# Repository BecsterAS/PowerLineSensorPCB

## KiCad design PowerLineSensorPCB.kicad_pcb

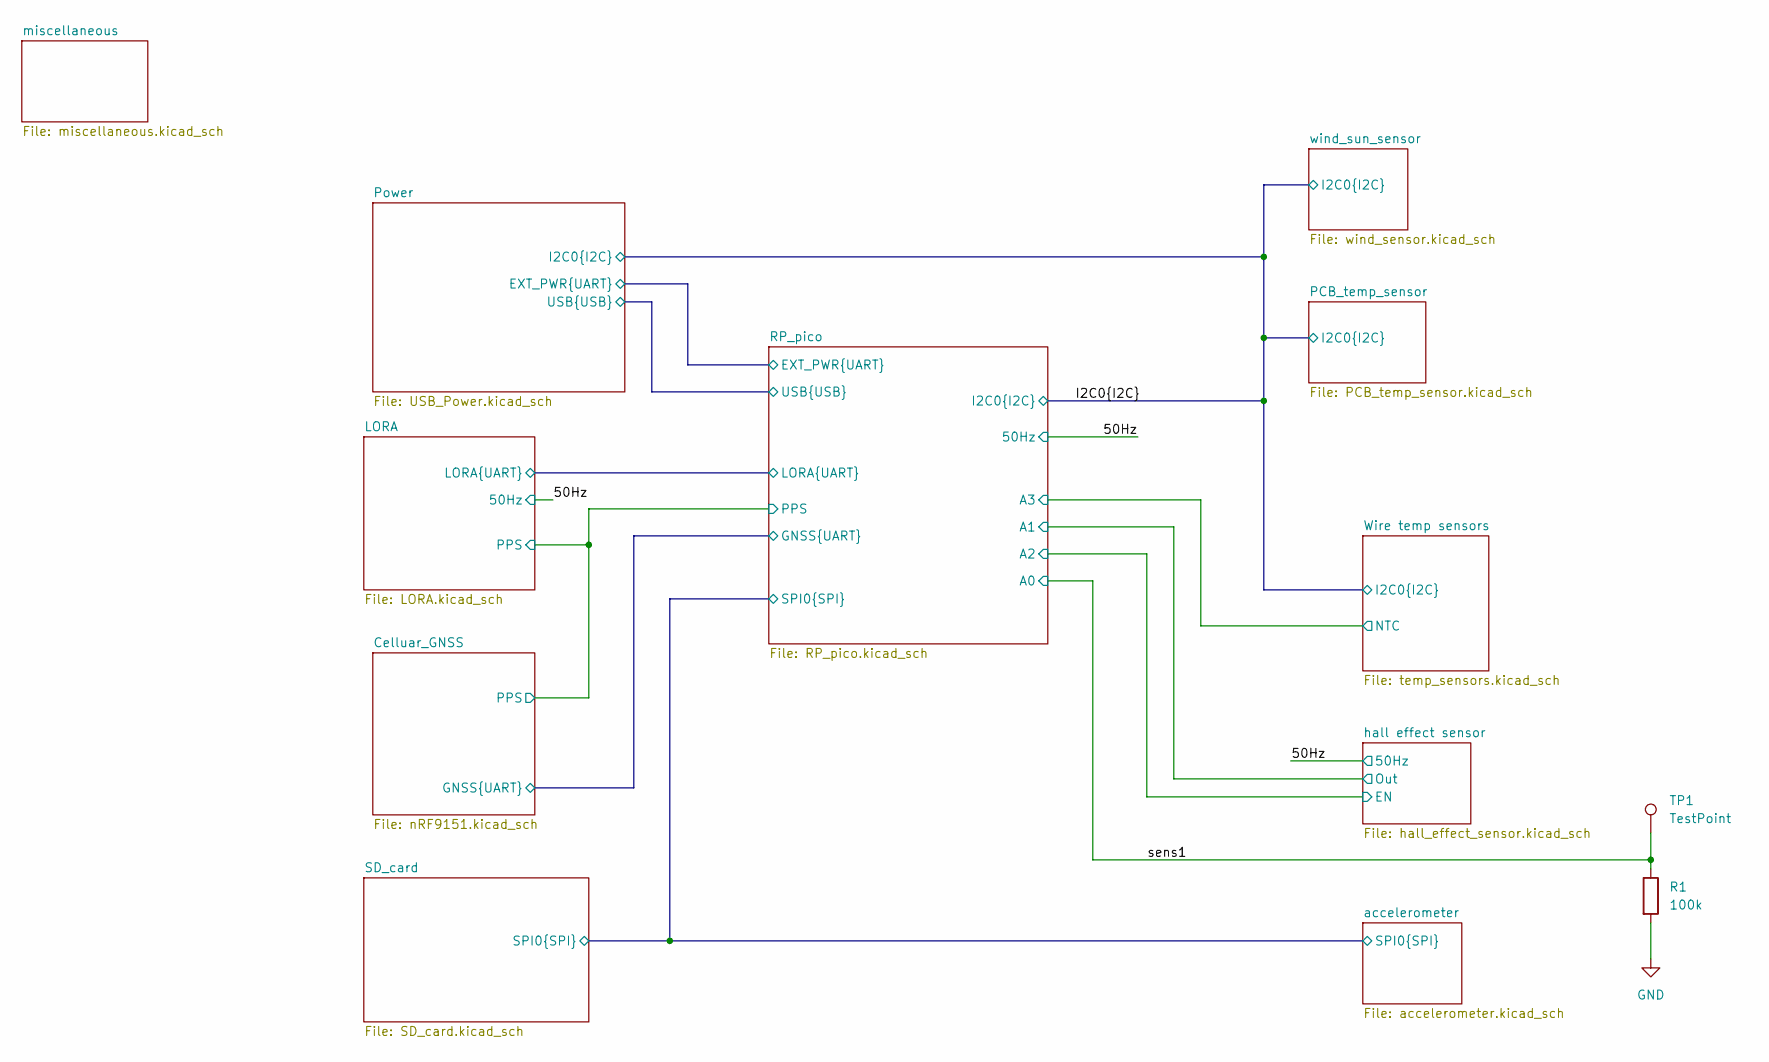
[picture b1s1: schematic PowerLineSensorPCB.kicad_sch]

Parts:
R1: 100k; R_0402_1005Metric; PartNumber 0402WGF1003TCE
TP1: TestPoint; TestPoint_Pad_D1.0mm

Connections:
/sens1: R1.1, TP1.1 (1_1); also elsewhere on the board
GND: R1.2; also elsewhere on the board

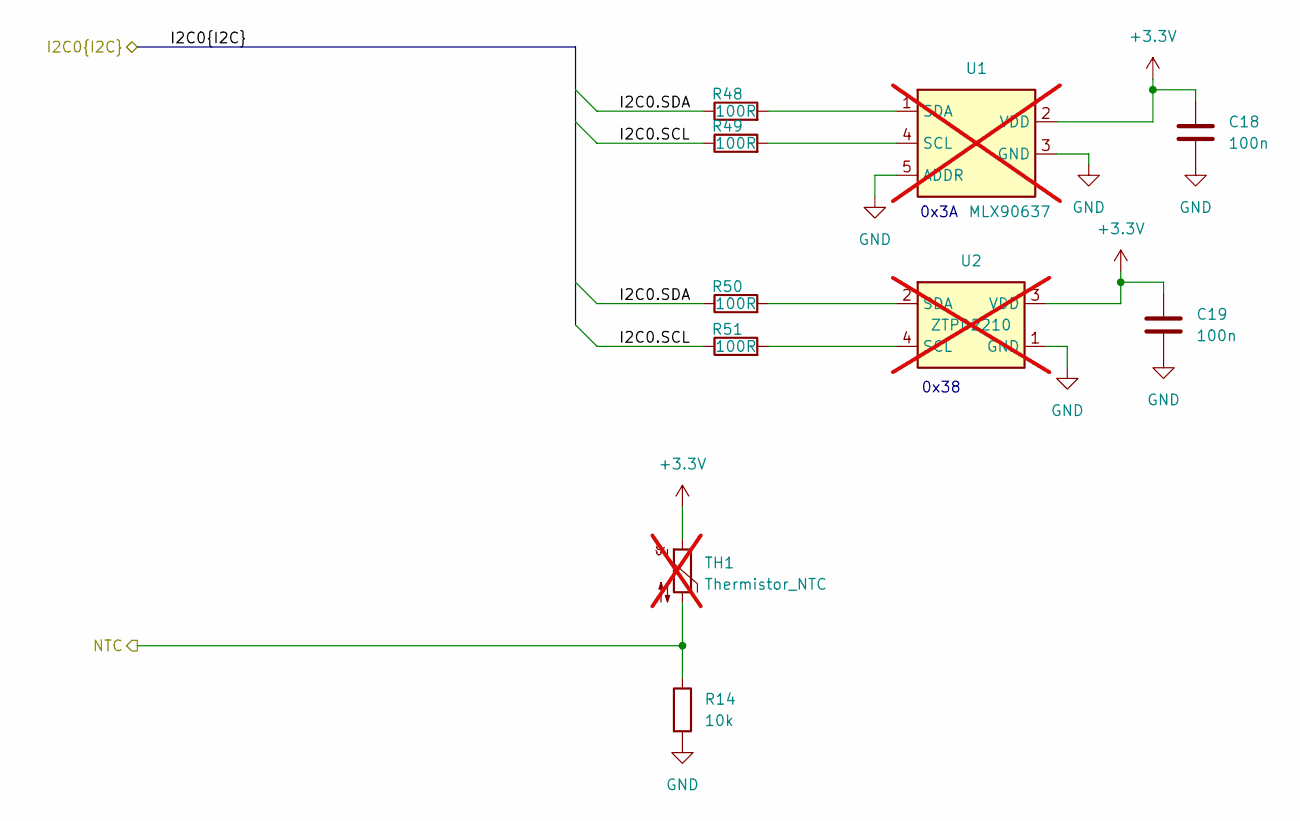
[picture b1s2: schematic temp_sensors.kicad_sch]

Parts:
C18, C19: 100n; C_0402_1005Metric; PartNumber CL05B104KO5NNNC
R14: 10k; R_0402_1005Metric; PartNumber 0402WGF1002TCE
R48, R49, R50, R51: 100R; R_0402_1005Metric; PartNumber 0402WGF1000TCE
TH1: Thermistor_NTC; R_Axial_DIN0204_L3.6mm_D1.6mm_P2.54mm_Vertical; not fitted
U1: MLX90637; PartNumber MLX90637; not fitted
U2: ZTPD2210; PartNumber ZTPD2210; not fitted

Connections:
+3.3V: C18.1, C19.1, TH1.1, U1.2 (VDD), U2.3 (VDD); also elsewhere on the board
/I2C0.SCL: R49.1, R51.1; also elsewhere on the board
/I2C0.SDA: R48.1, R50.1; also elsewhere on the board
/RP_pico/A3: R14.1, TH1.2; also elsewhere on the board
GND: C18.2, C19.2, R14.2, U1.3 (GND), U1.5 (ADDR), U1.6 (GND), U2.1 (GND); also elsewhere on the board
unnamed: R49.2, U1.4 (SCL)
unnamed: R48.2, U1.1 (SDA)
unnamed: R51.2, U2.4 (SCL)
unnamed: R50.2, U2.2 (SDA)

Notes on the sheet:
0x38
0x3A

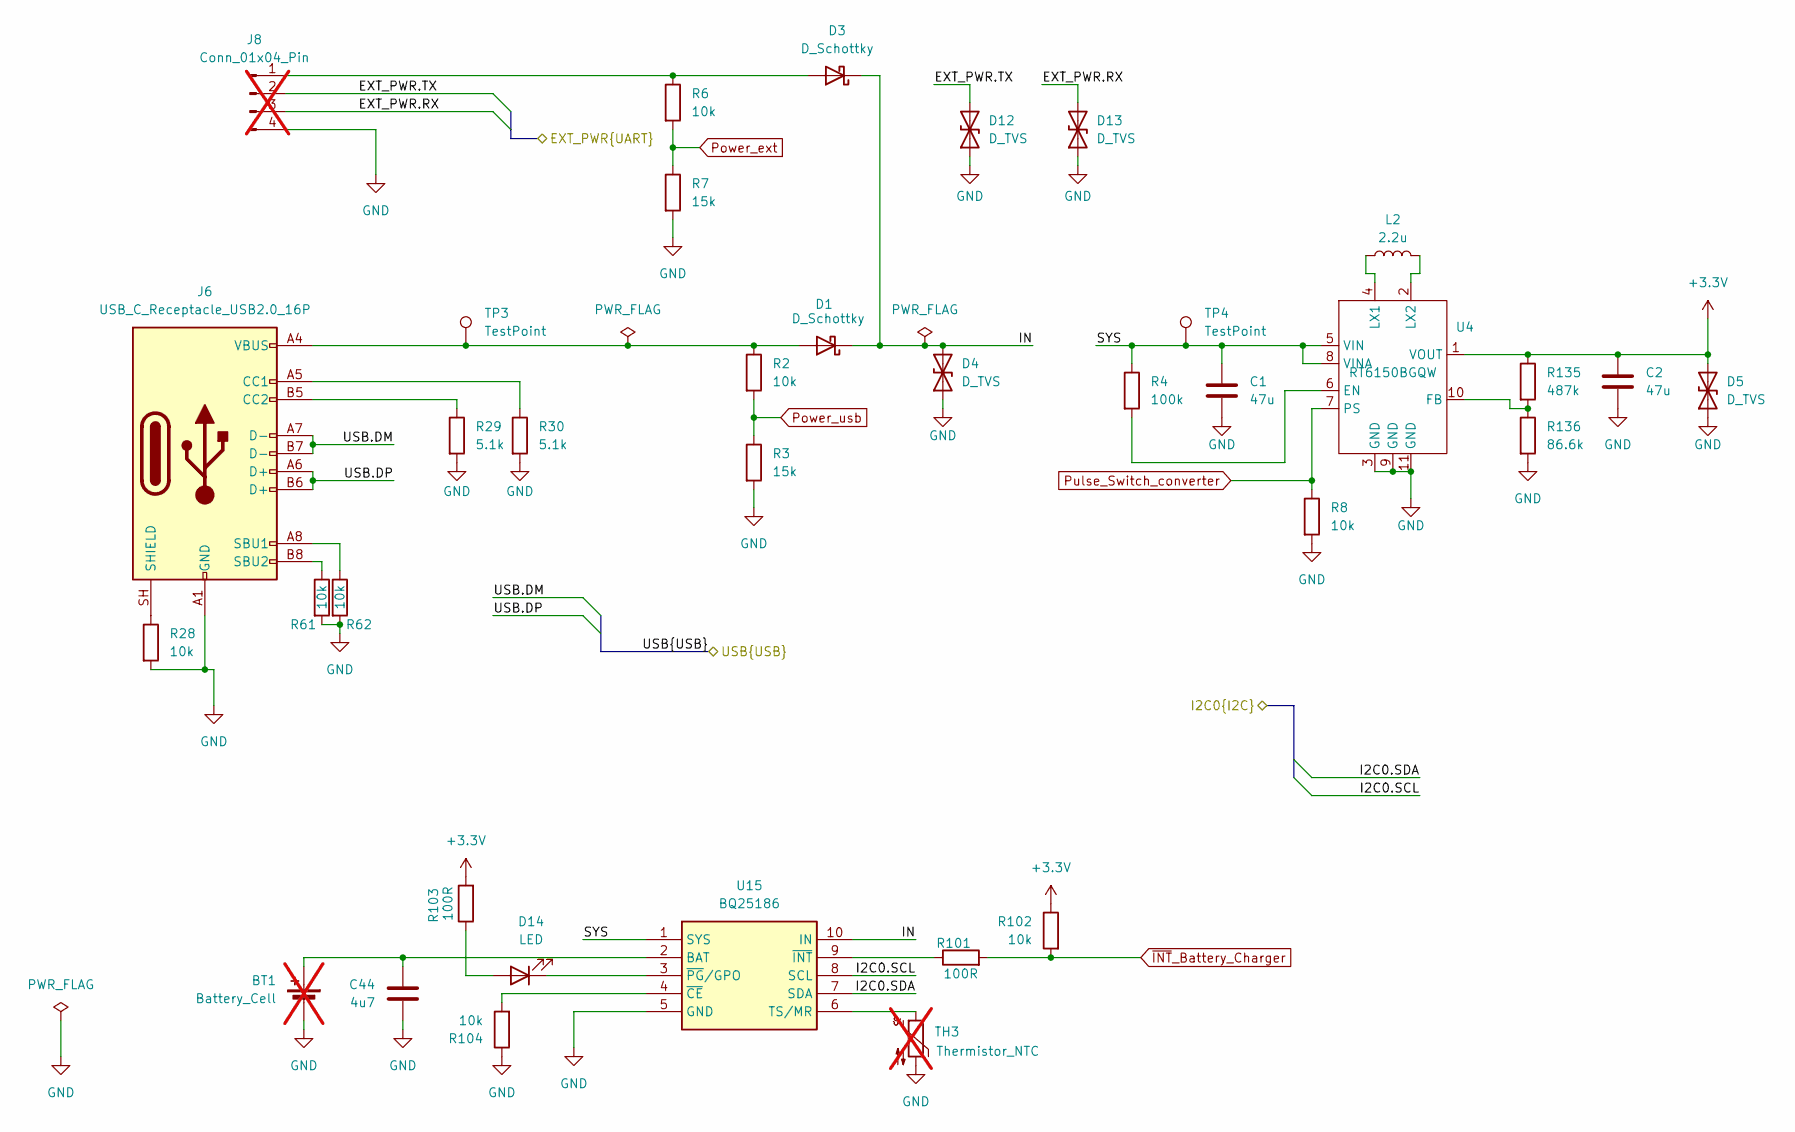
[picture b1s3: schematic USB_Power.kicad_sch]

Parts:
BT1: Battery_Cell; BatteryHolder_MPD_BH-18650-PC; PartNumber BH-18650-PC; not fitted
C1, C2: 47u; C_1206_3216Metric; PartNumber CL31A476MPHNNNE
C44: 4u7; C_0402_1005Metric; PartNumber CL05A475MP5NRNC
D1, D3: D_Schottky; D_SMA; PartNumber SS210
D4: D_TVS; D_SMB; PartNumber P6SMB6.8CA/TR13
D5, D12, D13: D_TVS; D_SOD-882; PartNumber PESD5V0C1ULS-QYL
D14: LED; D_0603_1608Metric; PartNumber KT-0603R
J6: USB_C_Receptacle_USB2.0_16P; USB_C_Receptacle_HRO_TYPE-C-31-M-12; PartNumber TYPE-C-31-M-12
J8: Conn_01x04_Pin; PinHeader_1x04_P2.54mm_Vertical; not fitted
L2: 2.2u; L_Murata_C2046258; PartNumber LQH3NPZ2R2MMEL
R2, R6, R8, R28, R61, R62, R102, R104: 10k; R_0402_1005Metric; PartNumber 0402WGF1002TCE
R3, R7: 15k; R_0402_1005Metric; PartNumber 0402WGF1502TCE
R4: 100k; R_0402_1005Metric; PartNumber 0402WGF1003TCE
R29, R30: 5.1k; R_0402_1005Metric; PartNumber 0402WGF5101TCE
R101, R103: 100R; R_0402_1005Metric; PartNumber 0402WGF1000TCE
R135: 487k; R_0402_1005Metric; PartNumber ERJ2RKF4873X
R136: 86.6k; R_0402_1005Metric; PartNumber ERA-2AEB8662X
TH3: Thermistor_NTC; R_0603_1608Metric_Pad0.98x0.95mm_HandSolder; not fitted
TP3, TP4: TestPoint; TestPoint_Pad_D1.0mm
U4: RT6150BGQW; WDFN-10-1EP_3x3mm_P0.5mm_EP1.8x2.5mm; PartNumber RT6150BGQW
U15: BQ25186; BQ25186DLHR_SON40P220X200X80-11N; PartNumber BQ25186DLHR; Mouser Part Number 595-BQ25186DLHR

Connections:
+3.3V: C2.1, D5.2 (A2), R102.1, R103.2, R135.1, U4.1 (VOUT); also elsewhere on the board
/I2C0.SCL: U15.8 (SCL); also elsewhere on the board
/I2C0.SDA: U15.7 (SDA); also elsewhere on the board
/Power/EXT_PWR.RX: D13.2 (A2), J8.3; also elsewhere on the board
/Power/EXT_PWR.TX: D12.2 (A2), J8.2; also elsewhere on the board
/Power/IN: D1.1 (K), D3.1 (K), D4.2 (A2), U15.10 (IN)
/Power/SYS: C1.1, R4.1, TP4.1 (1_1), U4.5 (VIN), U4.8 (VINA), U15.1 (SYS)
/Power/USB.DM: J6.A7 (D-), J6.B7 (D-); also elsewhere on the board
/Power/USB.DP: J6.A6 (D+), J6.B6 (D+); also elsewhere on the board
GND: BT1.2 (-), C1.2, C2.2, C44.2, D4.1 (A1), D5.1 (A1), D12.1 (A1), D13.1 (A1), J6.A1 (GND), J6.A12 (GND), J6.B1 (GND), J6.B12 (GND), J8.4, R3.2, R7.2, R8.2, R28.2, R29.2, R30.2, R61.2, R62.2, R104.1, R136.2, TH3.2, U4.3 (GND), U4.9 (GND), U4.11 (GND), U15.5 (GND), U15.11 (GND); also elsewhere on the board
unnamed: BT1.1 (+), C44.1, U15.2 (BAT)
unnamed: D1.2 (A), J6.A4 (VBUS), J6.A9 (VBUS), J6.B4 (VBUS), J6.B9 (VBUS), R2.1, TP3.1 (1_1)
unnamed: D3.2 (A), J8.1, R6.1
unnamed: D14.2 (A), R103.1
unnamed: D14.1 (K), U15.3 (~PG/GPO)
unnamed: J6.A5 (CC1), R30.1
unnamed: J6.B5 (CC2), R29.1
unnamed: J6.A8 (SBU1), R62.1
unnamed: J6.B8 (SBU2), R61.1
unnamed: J6.SH (SHIELD), R28.1
unnamed: R4.2, U4.6 (EN)
unnamed: R135.2, R136.1, U4.10 (FB)
unnamed: L2.1, U4.4 (LX1)
unnamed: L2.2, U4.2 (LX2)
unnamed: TH3.1, U15.6 (TS/MR)
unnamed: R104.2, U15.4 (~CE)
unnamed: R101.1, U15.9 (~INT)
Power_ext: R6.2, R7.1; also elsewhere on the board
Power_usb: R2.2, R3.1; also elsewhere on the board
Pulse_Switch_converter: R8.1, U4.7 (PS); also elsewhere on the board
~INT_Battery_Charger: R101.2, R102.2; also elsewhere on the board

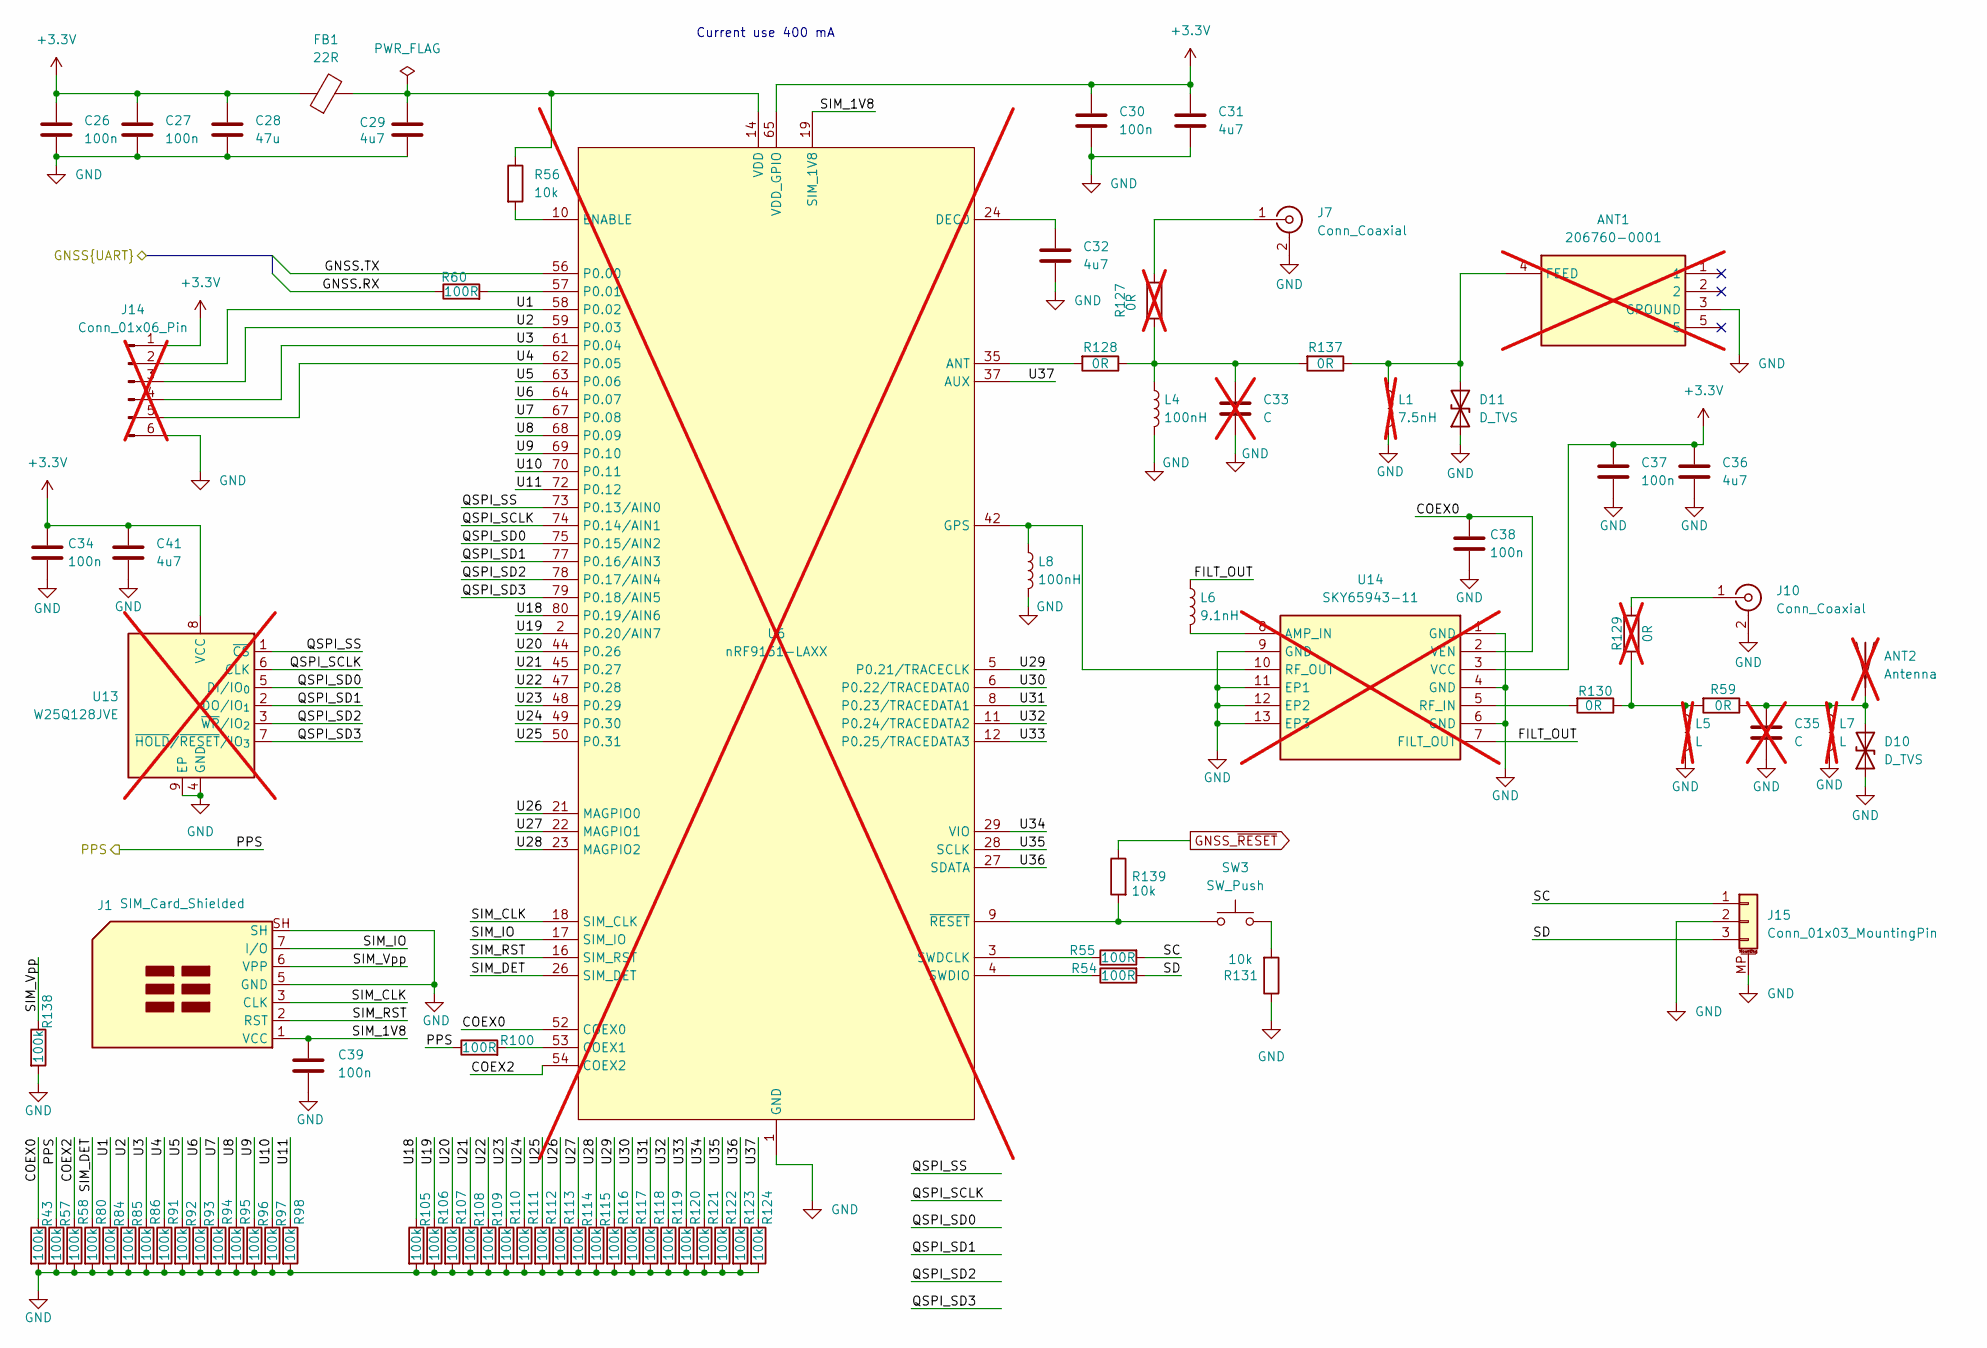
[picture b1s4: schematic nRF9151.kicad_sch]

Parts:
ANT1: 206760-0001; 2067600001; Mouser Part Number 538-206760-0001; not fitted
ANT2: Antenna; W3216; PartNumber W3216; not fitted
C26, C27, C30, C34, C37, C38, C39: 100n; C_0402_1005Metric; PartNumber CL05B104KO5NNNC
C28: 47u; C_1206_3216Metric; PartNumber CL31A476MPHNNNE
C29, C31, C32, C36, C41: 4u7; C_0402_1005Metric; PartNumber CL05A475MP5NRNC
C33, C35: C; C_0402_1005Metric; not fitted
D10, D11: D_TVS; Texas_DPY0002A_0.6x1mm_P0.65mm; PartNumber ESD701DPYR
FB1: 22R; L_0603_1608Metric; PartNumber BLM18SD220SN1D
J1: SIM_Card_Shielded; nanoSIM_GCT_SIM8060-6-0-14-00; PartNumber SIM8060-6-0-14-00-A
J7, J10: Conn_Coaxial; U.FL_Hirose_U.FL-R-SMT-1_Vertical; PartNumber BWU.FL-IPEX1
J14: Conn_01x06_Pin; PinHeader_1x06_P1.00mm_Vertical; not fitted
J15: Conn_01x03_MountingPin; JST_SH_BM03B-SRSS-TB_1x03-1MP_P1.00mm_Vertical; PartNumber BM03B-SRSS-TB(LF)(SN)
L1: 7.5nH; L_0402_1005Metric; not fitted
L4, L8: 100nH; L_0402_1005Metric; PartNumber LQW15ANR10J00D
L5, L7: L; L_0402_1005Metric; not fitted
L6: 9.1nH; L_0402_1005Metric; PartNumber LQW15AN9N1J00D
R43, R57, R58, R80, R84, R85, R86, R91, R92, R93, R94, R95, R96, R97, R98, R105, R106, R107, R108, R109, R110, R111, R112, R113, R114, R115, R116, R117, R118, R119, R120, R121, R122, R123, R124, R138: 100k; R_0402_1005Metric; PartNumber 0402WGF1003TCE
R54, R55, R60, R100: 100R; R_0402_1005Metric; PartNumber 0402WGF1000TCE
R56, R131, R139: 10k; R_0402_1005Metric; PartNumber 0402WGF1002TCE
R59, R128, R130, R137: 0R; R_0402_1005Metric; PartNumber 0402WGF0000TCE
R127, R129: 0R; R_0402_1005Metric; not fitted
SW3: SW_Push; SW_SPST_EVQP2_ShortPushTravel_H2.1mm; PartNumber EVQP2T02M
U6: nRF9151-LAXX; LGA_9151_12.1x11.1mm; PartNumber nRF9151-A1; not fitted
U13: W25Q128JVE; W25Q; PartNumber W25Q128JVEIM; not fitted
U14: SKY65943-11; SKY6594311; Mouser Part Number 873-SKY65943-11; not fitted

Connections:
+3.3V: C26.1, C27.1, C28.1, C30.1, C31.1, C34.1, C36.1, C37.1, C41.1, FB1.1, J14.1, U6.65 (VDD_GPIO), U13.8 (VCC), U14.3 (VCC); also elsewhere on the board
/Celluar_GNSS/COEX0: C38.1, R43.1, U6.52 (COEX0), U14.2 (VEN)
/Celluar_GNSS/COEX2: R58.1, U6.54 (COEX2)
/Celluar_GNSS/FILT_OUT: L6.1, U14.7 (FILT_OUT)
/Celluar_GNSS/GNSS.RX: R60.1; also elsewhere on the board
/Celluar_GNSS/GNSS.TX: U6.56 (P0.00); also elsewhere on the board
/Celluar_GNSS/PPS: R57.1, R100.1; also elsewhere on the board
/Celluar_GNSS/QSPI_SCLK: U6.74 (P0.14/AIN1), U13.6 (CLK)
/Celluar_GNSS/QSPI_SD0: U6.75 (P0.15/AIN2), U13.5 (DI/IO_{0})
/Celluar_GNSS/QSPI_SD1: U6.77 (P0.16/AIN3), U13.2 (DO/IO_{1})
/Celluar_GNSS/QSPI_SD2: U6.78 (P0.17/AIN4), U13.3 (~WP/IO_{2})
/Celluar_GNSS/QSPI_SD3: U6.79 (P0.18/AIN5), U13.7 (~HOLD/~RESET/IO_{3})
/Celluar_GNSS/QSPI_SS: U6.73 (P0.13/AIN0), U13.1 (~CS)
/Celluar_GNSS/SC: J15.1, R55.2
/Celluar_GNSS/SD: J15.3, R54.2
/Celluar_GNSS/SIM_1V8: C39.1, J1.1 (VCC), U6.19 (SIM_1V8)
/Celluar_GNSS/SIM_CLK: J1.3 (CLK), U6.18 (SIM_CLK)
/Celluar_GNSS/SIM_DET: R80.1, U6.26 (SIM_DET)
/Celluar_GNSS/SIM_IO: J1.7 (I/O), U6.17 (SIM_IO)
/Celluar_GNSS/SIM_RST: J1.2 (RST), U6.16 (SIM_RST)
/Celluar_GNSS/SIM_Vpp: J1.6 (VPP), R138.1
/Celluar_GNSS/U1: J14.2, R84.1, U6.58 (P0.02)
/Celluar_GNSS/U2: J14.3, R85.1, U6.59 (P0.03)
/Celluar_GNSS/U3: J14.4, R86.1, U6.61 (P0.04)
/Celluar_GNSS/U4: J14.5, R91.1, U6.62 (P0.05)
/Celluar_GNSS/U5: R92.1, U6.63 (P0.06)
/Celluar_GNSS/U6: R93.1, U6.64 (P0.07)
/Celluar_GNSS/U7: R94.1, U6.67 (P0.08)
/Celluar_GNSS/U8: R95.1, U6.68 (P0.09)
/Celluar_GNSS/U9: R96.1, U6.69 (P0.10)
/Celluar_GNSS/U10: R97.1, U6.70 (P0.11)
/Celluar_GNSS/U11: R98.1, U6.72 (P0.12)
/Celluar_GNSS/U18: R105.1, U6.80 (P0.19/AIN6)
/Celluar_GNSS/U19: R106.1, U6.2 (P0.20/AIN7)
/Celluar_GNSS/U20: R107.1, U6.44 (P0.26)
/Celluar_GNSS/U21: R108.1, U6.45 (P0.27)
/Celluar_GNSS/U22: R109.1, U6.47 (P0.28)
/Celluar_GNSS/U23: R110.1, U6.48 (P0.29)
/Celluar_GNSS/U24: R111.1, U6.49 (P0.30)
/Celluar_GNSS/U25: R112.1, U6.50 (P0.31)
/Celluar_GNSS/U26: R113.1, U6.21 (MAGPIO0)
/Celluar_GNSS/U27: R114.1, U6.22 (MAGPIO1)
/Celluar_GNSS/U28: R115.1, U6.23 (MAGPIO2)
/Celluar_GNSS/U29: R116.1, U6.5 (P0.21/TRACECLK)
/Celluar_GNSS/U30: R117.1, U6.6 (P0.22/TRACEDATA0)
/Celluar_GNSS/U31: R118.1, U6.8 (P0.23/TRACEDATA1)
/Celluar_GNSS/U32: R119.1, U6.11 (P0.24/TRACEDATA2)
/Celluar_GNSS/U33: R120.1, U6.12 (P0.25/TRACEDATA3)
/Celluar_GNSS/U34: R121.1, U6.29 (VIO)
/Celluar_GNSS/U35: R122.1, U6.28 (SCLK)
/Celluar_GNSS/U36: R123.1, U6.27 (SDATA)
/Celluar_GNSS/U37: R124.1, U6.37 (AUX)
GND: ANT1.3 (GROUND), C26.2, C27.2, C28.2, C29.2, C30.2, C31.2, C32.2, C33.2, C34.2, C35.2, C36.2, C37.2, C38.2, C39.2, C41.2, D10.1 (A1), D11.1 (A1), J1.5 (GND), J1.SH, J7.2 (Ext), J10.2 (Ext), J14.6, J15.2, J15.MP (MountPin), L1.2, L4.2, L5.2, L7.2, L8.2, R43.2, R57.2, R58.2, R80.2, R84.2, R85.2, R86.2, R91.2, R92.2, R93.2, R94.2, R95.2, R96.2, R97.2, R98.2, R105.2, R106.2, R107.2, R108.2, R109.2, R110.2, R111.2, R112.2, R113.2, R114.2, R115.2, R116.2, R117.2, R118.2, R119.2, R120.2, R121.2, R122.2, R123.2, R124.2, R131.1, R138.2, U6.1 (GND), U6.7 (GND), U6.13 (GND), U6.15 (GND), U6.20 (GND), U6.25 (GND), U6.30 (GND), U6.34 (GND), U6.36 (GND), U6.38 (GND), U6.39 (GND), U6.40 (GND), U6.41 (GND), U6.43 (GND), U6.46 (GND), U6.51 (GND), U6.55 (GND), U6.60 (GND), U6.66 (GND), U6.71 (GND), U6.76 (GND), U6.105 (GND), U6.106 (GND), U6.107 (GND), U6.108 (GND), U6.109 (GND), U6.110 (GND), U6.111 (GND), U6.112 (GND), U6.113 (GND), U13.4 (GND), U13.9 (EP), U14.1 (GND), U14.4 (GND), U14.6 (GND), U14.9 (GND), U14.11 (EP1), U14.12 (EP2), U14.13 (EP3); also elsewhere on the board
GNSS_~RESET: R139.1; also elsewhere on the board
unnamed: ANT1.4 (FEED), D11.2 (A2), L1.1, R137.1
unnamed: ANT2.1 (A_1), C35.1, D10.2 (A2), L7.1, R59.1
unnamed: C33.1, L4.1, R127.2, R128.1, R137.2
unnamed: J7.1 (In), R127.1
unnamed: J10.1 (In), R129.1
unnamed: L5.1, R59.2, R129.2, R130.1
unnamed: R131.2, SW3.2
unnamed: R128.2, U6.35 (ANT)
unnamed: R100.2, U6.53 (COEX1)
unnamed: C32.1, U6.24 (DEC0)
unnamed: R56.2, U6.10 (ENABLE)
unnamed: R60.2, U6.57 (P0.01)
unnamed: R55.1, U6.3 (SWDCLK)
unnamed: R54.1, U6.4 (SWDIO)
unnamed: C29.1, FB1.2, R56.1, U6.14 (VDD)
unnamed: R139.2, SW3.1, U6.9 (~RESET)
unnamed: L6.2, U14.8 (AMP_IN)
unnamed: R130.2, U14.5 (RF_IN)
unnamed: L8.1, U6.42 (GPS), U14.10 (RF_OUT)

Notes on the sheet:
Current use 400 mA

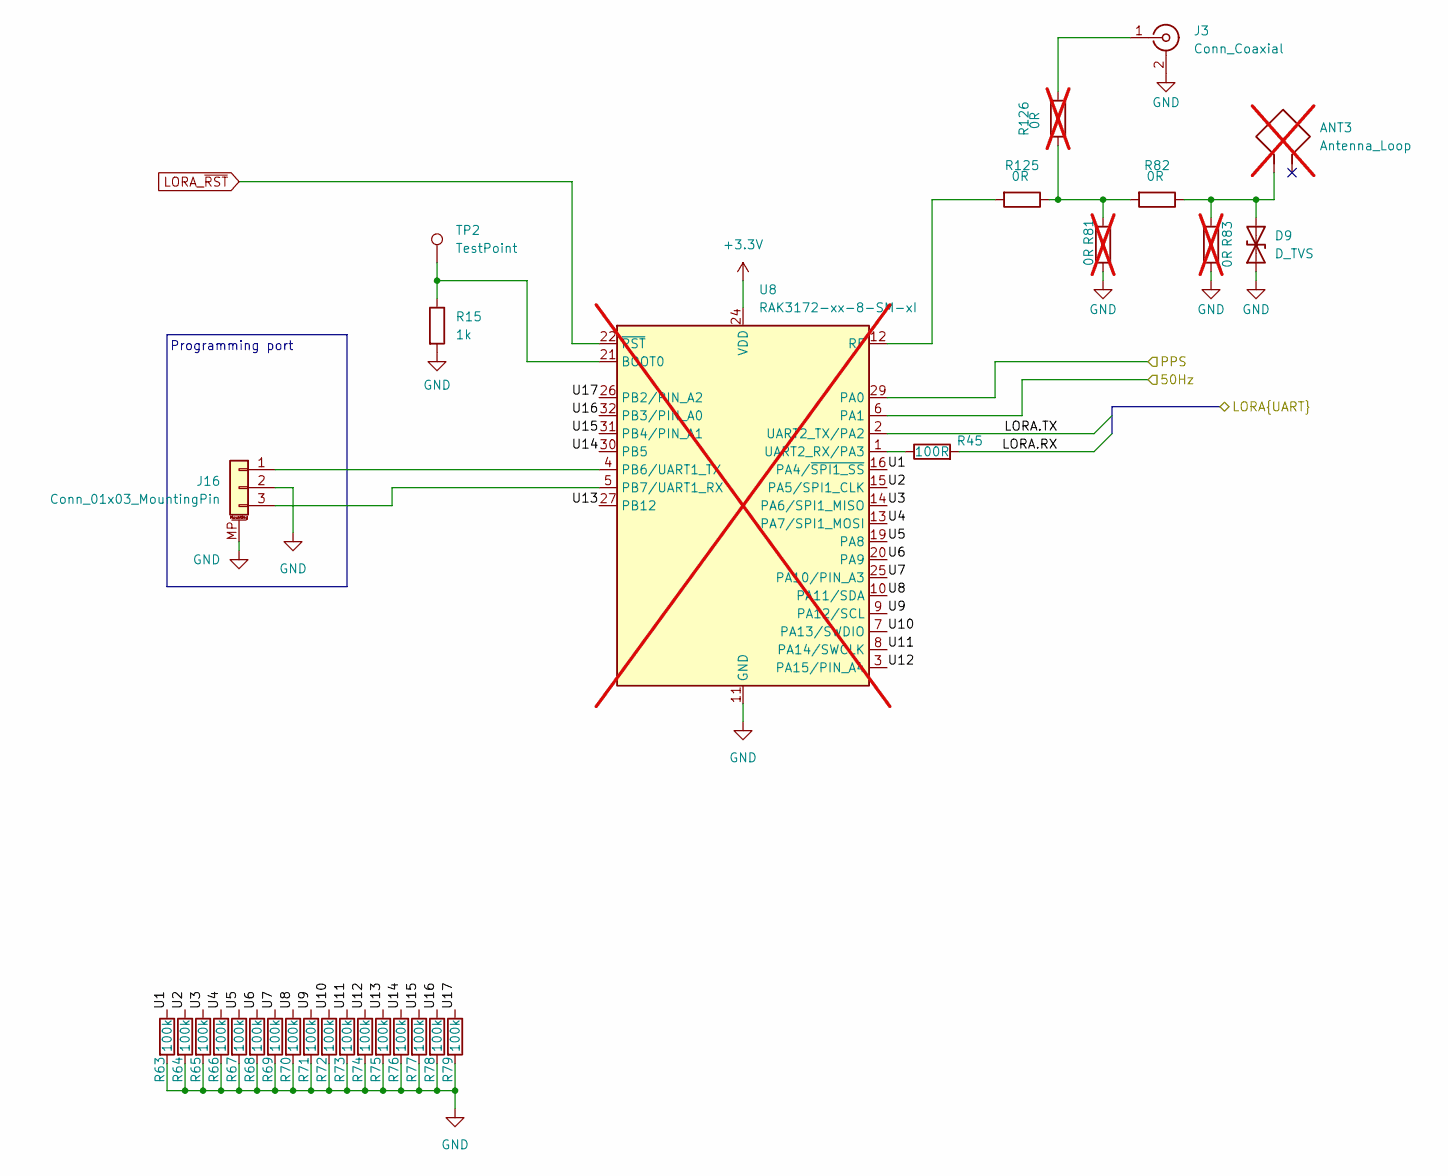
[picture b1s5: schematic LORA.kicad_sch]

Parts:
ANT3: Antenna_Loop; ANT-868-HESM; PartNumber ANT-868-HESM; not fitted
D9: D_TVS; Texas_DPY0002A_0.6x1mm_P0.65mm; PartNumber ESD701DPYR
J3: Conn_Coaxial; U.FL_Hirose_U.FL-R-SMT-1_Vertical; PartNumber BWU.FL-IPEX1
J16: Conn_01x03_MountingPin; JST_SH_BM03B-SRSS-TB_1x03-1MP_P1.00mm_Vertical; PartNumber BM03B-SRSS-TB(LF)(SN)
R15: 1k; R_0402_1005Metric; PartNumber 0402WGF1001TCE
R45: 100R; R_0402_1005Metric; PartNumber 0402WGF1000TCE
R63, R64, R65, R66, R67, R68, R69, R70, R71, R72, R73, R74, R75, R76, R77, R78, R79: 100k; R_0402_1005Metric; PartNumber 0402WGF1003TCE
R81, R83, R126: 0R; R_0402_1005Metric; not fitted
R82, R125: 0R; R_0402_1005Metric; PartNumber 0402WGF0000TCE
TP2: TestPoint; TestPoint_Pad_D1.0mm
U8: RAK3172-xx-8-SM-xI; RAK3172; PartNumber RAK3172-T-8-SM-NI; not fitted

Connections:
+3.3V: U8.24 (VDD); also elsewhere on the board
/50Hz: U8.6 (PA1); also elsewhere on the board
/Celluar_GNSS/PPS: U8.29 (PA0); also elsewhere on the board
/LORA/LORA.RX: R45.2; also elsewhere on the board
/LORA/LORA.TX: U8.2 (UART2_TX/PA2); also elsewhere on the board
/LORA/U1: R63.1, U8.16 (PA4/~SPI1_SS)
/LORA/U2: R64.1, U8.15 (PA5/SPI1_CLK)
/LORA/U3: R65.1, U8.14 (PA6/SPI1_MISO)
/LORA/U4: R66.1, U8.13 (PA7/SPI1_MOSI)
/LORA/U5: R67.1, U8.19 (PA8)
/LORA/U6: R68.1, U8.20 (PA9)
/LORA/U7: R69.1, U8.25 (PA10/PIN_A3)
/LORA/U8: R70.1, U8.10 (PA11/SDA)
/LORA/U9: R71.1, U8.9 (PA12/SCL)
/LORA/U10: R72.1, U8.7 (PA13/SWDIO)
/LORA/U11: R73.1, U8.8 (PA14/SWCLK)
/LORA/U12: R74.1, U8.3 (PA15/PIN_A4)
/LORA/U13: R75.1, U8.27 (PB12)
/LORA/U14: R76.1, U8.30 (PB5)
/LORA/U15: R77.1, U8.31 (PB4/PIN_A1)
/LORA/U16: R78.1, U8.32 (PB3/PIN_A0)
/LORA/U17: R79.1, U8.26 (PB2/PIN_A2)
GND: D9.1 (A1), J3.2 (Ext), J16.2, J16.MP (MountPin), R15.2, R63.2, R64.2, R65.2, R66.2, R67.2, R68.2, R69.2, R70.2, R71.2, R72.2, R73.2, R74.2, R75.2, R76.2, R77.2, R78.2, R79.2, R81.2, R83.1, U8.11 (GND), U8.17 (GND), U8.18 (GND), U8.23 (GND), U8.28 (GND); also elsewhere on the board
LORA_~RST: U8.22 (~RST); also elsewhere on the board
unnamed: ANT3.1, D9.2 (A2), R82.1, R83.2
unnamed: J3.1 (In), R126.1
unnamed: J16.1, U8.4 (PB6/UART1_TX)
unnamed: J16.3, U8.5 (PB7/UART1_RX)
unnamed: R81.1, R82.2, R125.1, R126.2
unnamed: R15.1, TP2.1 (1_1), U8.21 (BOOT0)
unnamed: R125.2, U8.12 (RF)
unnamed: R45.1, U8.1 (UART2_RX/PA3)

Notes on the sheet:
Programming port

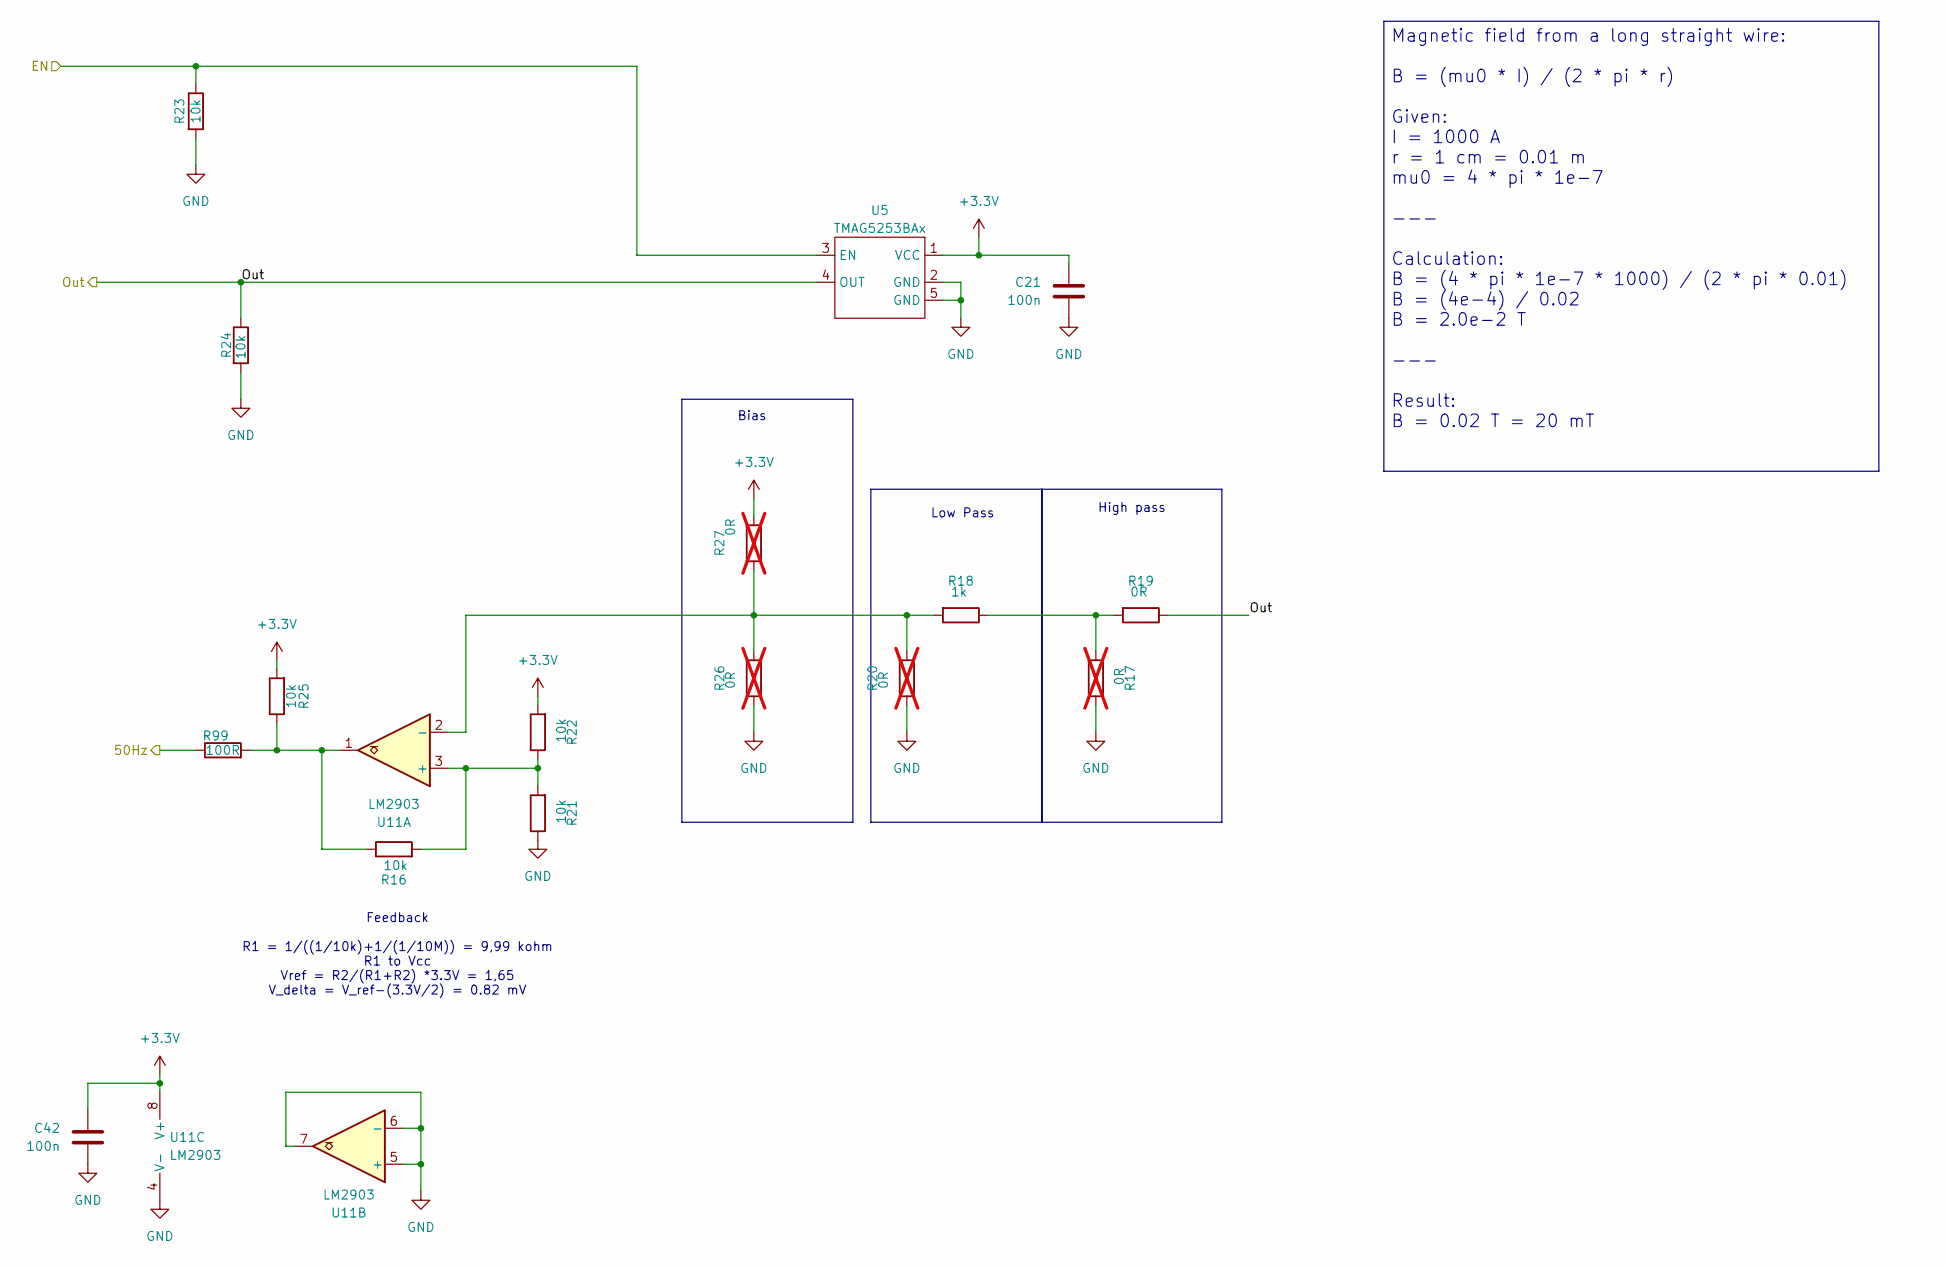
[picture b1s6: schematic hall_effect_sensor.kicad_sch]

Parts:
C21, C42: 100n; C_0402_1005Metric; PartNumber CL05B104KO5NNNC
R16, R21, R22, R23, R24, R25: 10k; R_0402_1005Metric; PartNumber 0402WGF1002TCE
R17, R20, R26, R27: 0R; R_0402_1005Metric; not fitted
R18: 1k; R_0402_1005Metric; PartNumber 0402WGF1001TCE
R19: 0R; R_0402_1005Metric; PartNumber 0402WGF0000TCE
R99: 100R; R_0402_1005Metric; PartNumber 0402WGF1000TCE
U5: TMAG5253BAx; Texas_X2SON-4-1EP_1.1x1.4mm_P0.5mm_EP0.8x0.6mm; PartNumber TMAG5253BA1
U11: LM2903; SOIC-8_3.9x4.9mm_P1.27mm; PartNumber LM2903DR

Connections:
+3.3V: C21.1, C42.1, R22.2, R25.2, R27.1, U5.1 (VCC), U11.8 (V+); also elsewhere on the board
/50Hz: R99.1; also elsewhere on the board
/RP_pico/A2: R23.1, U5.3 (EN); also elsewhere on the board
/hall effect sensor/Out: R19.1, R24.1, U5.4 (OUT); also elsewhere on the board
GND: C21.2, C42.2, R17.1, R20.2, R21.1, R23.2, R24.2, R26.2, U5.2 (GND), U5.5 (GND), U11.4 (V-), U11.5 (+), U11.6 (-), U11.7; also elsewhere on the board
unnamed: R16.1, R25.1, R99.2, U11.1
unnamed: R17.2, R18.1, R19.2
unnamed: R16.2, R21.2, R22.1, U11.3 (+)
unnamed: R18.2, R20.1, R26.1, R27.2, U11.2 (-)

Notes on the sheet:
Bias
High pass
Feedback R1 = 1/((1/10k)+1/(1/10M)) = 9,99 kohm R1 to Vcc Vref = R2/(R1+R2) *3.3V = 1,65 V_delta = V_ref-(3.3V/2) = 0.82 mV
Low Pass
Magnetic field from a long straight wire: B = (mu0 * I) / (2 * pi * r) Given: I = 1000 A r = 1 cm = 0.01 m mu0 = 4 * pi * 1e-7 --- Calculation: B = (4 * pi * 1e-7 * 1000) / (2 * pi * 0.01) B = (4e-4) / 0.02 B = 2.0e-2 T --- Result: B = 0.02 T = 20 mT

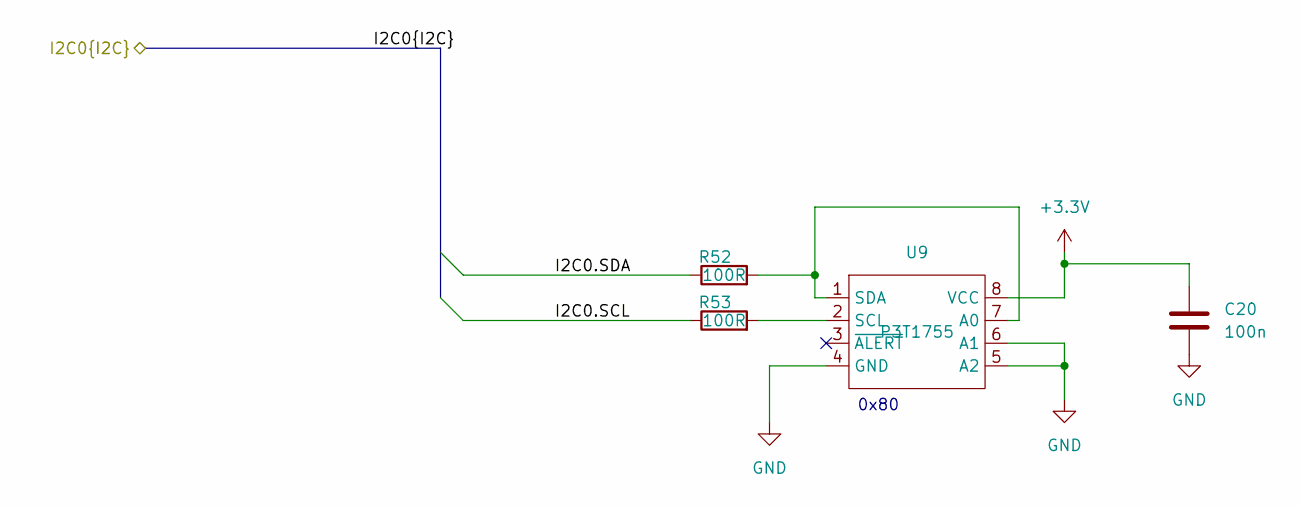
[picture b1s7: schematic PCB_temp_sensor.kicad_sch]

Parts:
C20: 100n; C_0402_1005Metric; PartNumber CL05B104KO5NNNC
R52, R53: 100R; R_0402_1005Metric; PartNumber 0402WGF1000TCE
U9: P3T1755; TSSOP-8_3x3mm_P0.65mm; PartNumber P3T1755 DP

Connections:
+3.3V: C20.1, U9.8 (VCC); also elsewhere on the board
/I2C0.SCL: R53.1; also elsewhere on the board
/I2C0.SDA: R52.1; also elsewhere on the board
GND: C20.2, U9.4 (GND), U9.5 (A2), U9.6 (A1); also elsewhere on the board
unnamed: R52.2, U9.1 (SDA), U9.7 (A0)
unnamed: R53.2, U9.2 (SCL)

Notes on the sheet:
0x80

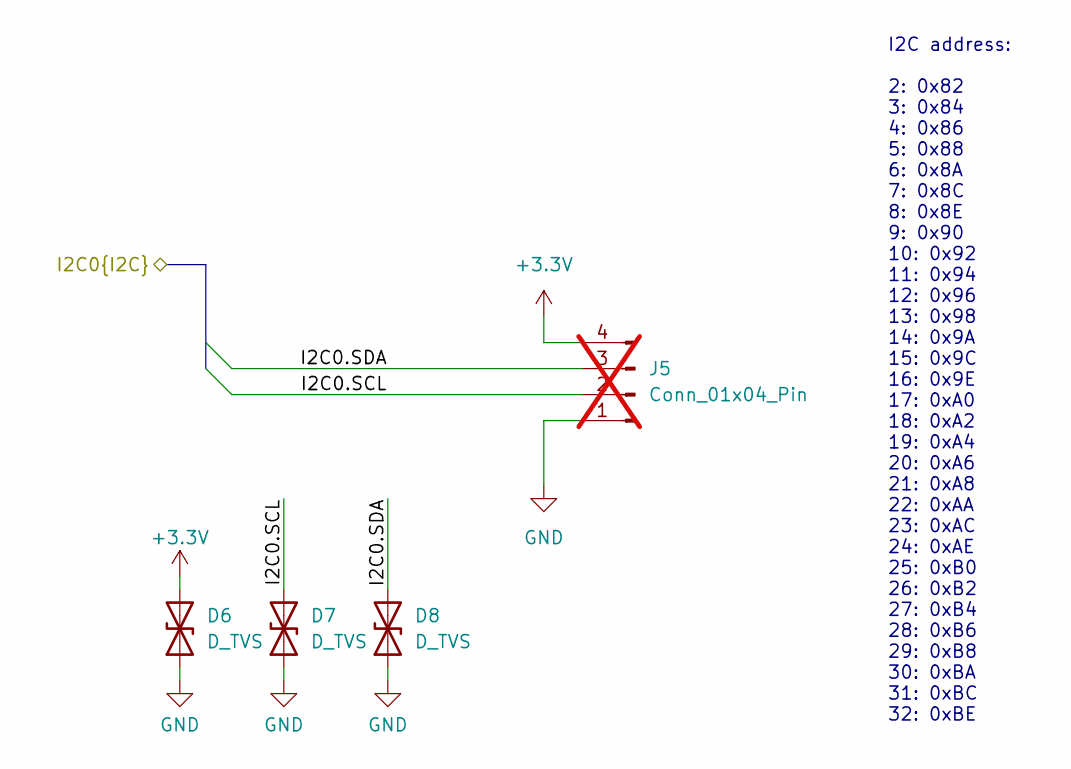
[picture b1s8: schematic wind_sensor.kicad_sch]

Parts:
D6, D7, D8: D_TVS; D_SOD-882; PartNumber PESD5V0C1ULS-QYL
J5: Conn_01x04_Pin; PinHeader_2x02_P2.54mm_Vertical; not fitted

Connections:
+3.3V: D6.2 (A2), J5.4; also elsewhere on the board
/I2C0.SCL: D7.2 (A2), J5.2; also elsewhere on the board
/I2C0.SDA: D8.2 (A2), J5.3; also elsewhere on the board
GND: D6.1 (A1), D7.1 (A1), D8.1 (A1), J5.1; also elsewhere on the board

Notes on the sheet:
I2C address: 2: 0x82 3: 0x84 4: 0x86 5: 0x88 6: 0x8A 7: 0x8C 8: 0x8E 9: 0x90 10: 0x92 11: 0x94 12: 0x96 13: 0x98 14: 0x9A 15: 0x9C 16: 0x9E 17: 0xA0 18: 0xA2 19: 0xA4 20: 0xA6 21: 0xA8 22: 0xAA 23: 0xAC 24: 0xAE 25: 0xB0 26: 0xB2 27: 0xB4 28: 0xB6 29: 0xB8 30: 0xBA 31: 0xBC 32: 0xBE

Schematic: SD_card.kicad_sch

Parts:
C17: 100n; C_0402_1005Metric; PartNumber CL05B104KO5NNNC
J2: Micro_SD_Card; microSD_HC_Molex_47219-2001; PartNumber 472192001
R35: 10k; R_0402_1005Metric; PartNumber 0402WGF1002TCE
R36: 100R; R_0402_1005Metric; PartNumber 0402WGF1000TCE

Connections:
+3.3V: C17.1, J2.4 (VDD), R35.1; also elsewhere on the board
/RP_pico/SPI0.RX: R36.1; also elsewhere on the board
/RP_pico/SPI0.SCK: J2.5 (CLK); also elsewhere on the board
/RP_pico/SPI0.TX: J2.3 (CMD); also elsewhere on the board
GND: C17.2, J2.6 (VSS), J2.SH (SHIELD); also elsewhere on the board
unnamed: J2.7 (DAT0), R36.2
~CS_SDCard: J2.2 (DAT3/CD), R35.2; also elsewhere on the board
